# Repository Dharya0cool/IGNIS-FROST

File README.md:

# Ignis Frost 🚀❄️

I designed **Ignis Frost** from scratch because I wanted a real, reliable flight computer for my model rockets instead of a fragile breadboard full of loose jumper wires. 

The name comes from the extreme contrast a rocket faces during launch: blistering engine heat at liftoff (*Ignis*) meeting freezing air high up in the atmosphere (*Frost*). Everything is packed onto a single compact circuit board built to fit inside a rocket airframe and survive the stress of flight.

## What It Does
* **Tracks Altitude Live:** Uses a BMP390 barometric pressure sensor to measure climb rate and height down to centimeters.
* **Senses Motion:** An onboard 6-axis IMU tracks acceleration and tilt throughout boost, coast, and descent.
* **Logs Flight Data:** Saves telemetry (`CSV`) to onboard storage so I can pull the data after landing and graph the flight curve.
* **Deploys the Parachute:** Automatically detects the exact second the rocket hits apogee (peak height) and triggers a MOSFET switch to fire the parachute ejection charge.

## Hardware Specs
* **Brain:** ESP32-C3-MINI-1
* **Barometer:** BMP390
* **Motion Sensor (IMU):** 6-Axis Accelerometer & Gyroscope
* **Power & Recovery:** 3.3V LDO Regulator + N-Channel MOSFET Ejection Circuit
* **Designed In:** KiCad 8

## What's in This Repo
* `/hardware` — KiCad schematic, PCB layout, and Gerber files for manufacturing
* `/bom` — Full parts list and sourcing links
* `/firmware` — Flight control, sensor filtering, and data-logging code

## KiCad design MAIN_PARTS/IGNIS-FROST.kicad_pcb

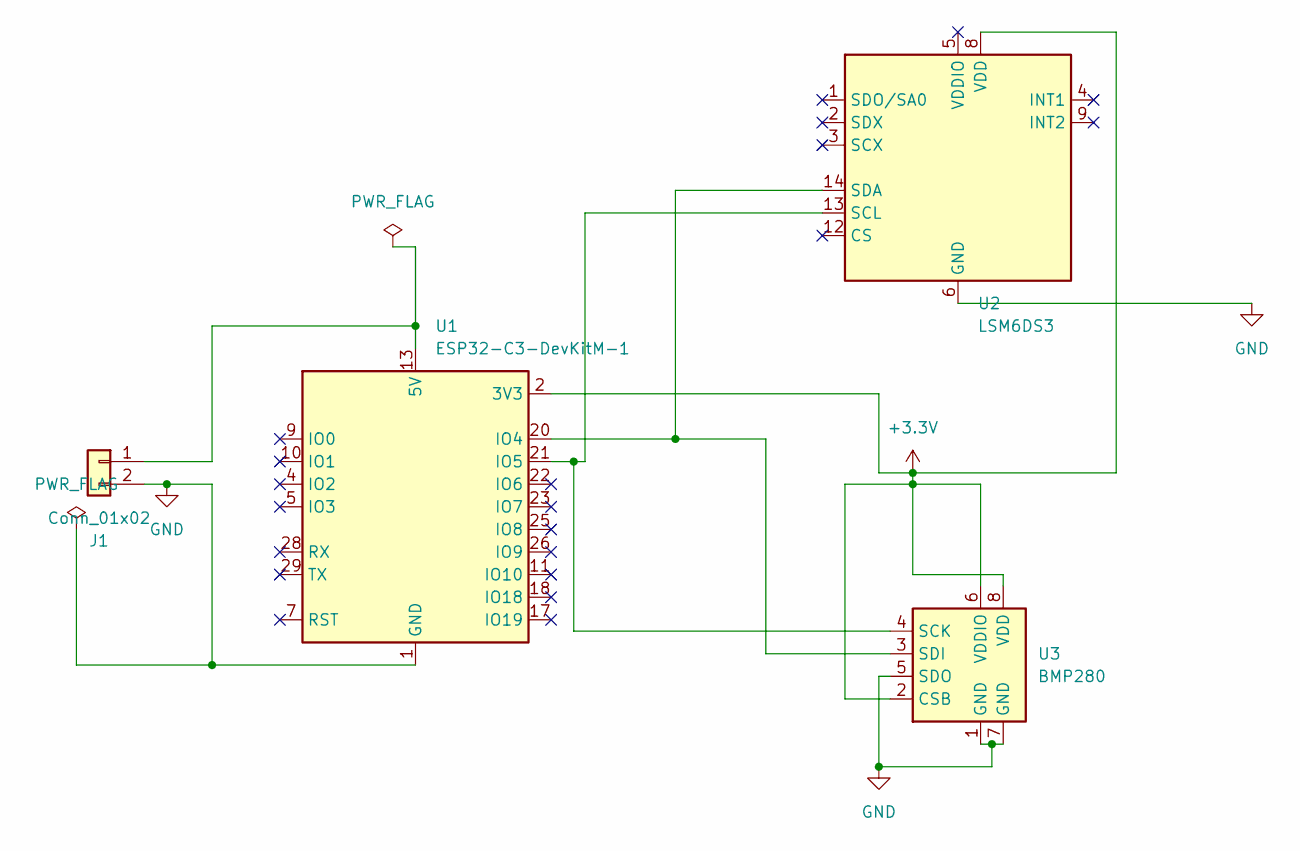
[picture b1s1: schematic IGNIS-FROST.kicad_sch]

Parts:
J1: Conn_01x02; JST_PH_B9B-PH-K_1x09_P2.00mm_Vertical
U1: ESP32-C3-DevKitM-1
U2: LSM6DS3; LGA-14_3x2.5mm_P0.5mm_LayoutBorder3x4y
U3: BMP280; Bosch_LGA-8_2x2.5mm_P0.65mm_ClockwisePinNumbering

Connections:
+3.3V: U1.2 (3V3), U1.3 (3V3), U2.8 (VDD), U3.2 (CSB), U3.6 (VDDIO), U3.8 (VDD)
GND: J1.2, U1.1 (GND), U1.6 (GND), U1.8 (GND), U1.12 (GND), U1.15 (GND), U1.16 (GND), U1.19 (GND), U1.24 (GND), U1.27 (GND), U1.30 (GND), U2.6 (GND), U2.7 (GND), U3.1 (GND), U3.5 (SDO), U3.7 (GND)
unnamed: J1.1, U1.13 (5V), U1.14 (5V)
unnamed: U1.20 (IO4), U2.14 (SDA), U3.3 (SDI)
unnamed: U1.21 (IO5), U2.13 (SCL), U3.4 (SCK)

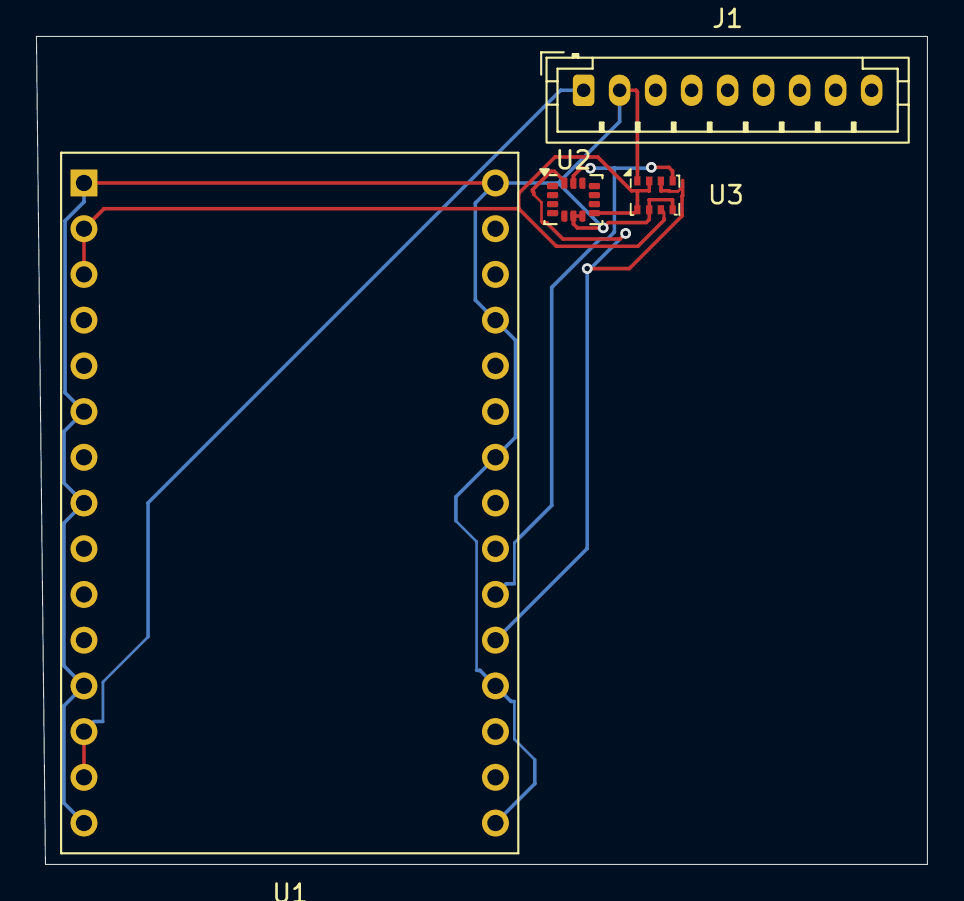
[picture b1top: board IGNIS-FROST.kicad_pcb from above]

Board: 2 copper layers, 49.5 x 46.0 mm, 4 parts (0 on the bottom side), 5 nets.
